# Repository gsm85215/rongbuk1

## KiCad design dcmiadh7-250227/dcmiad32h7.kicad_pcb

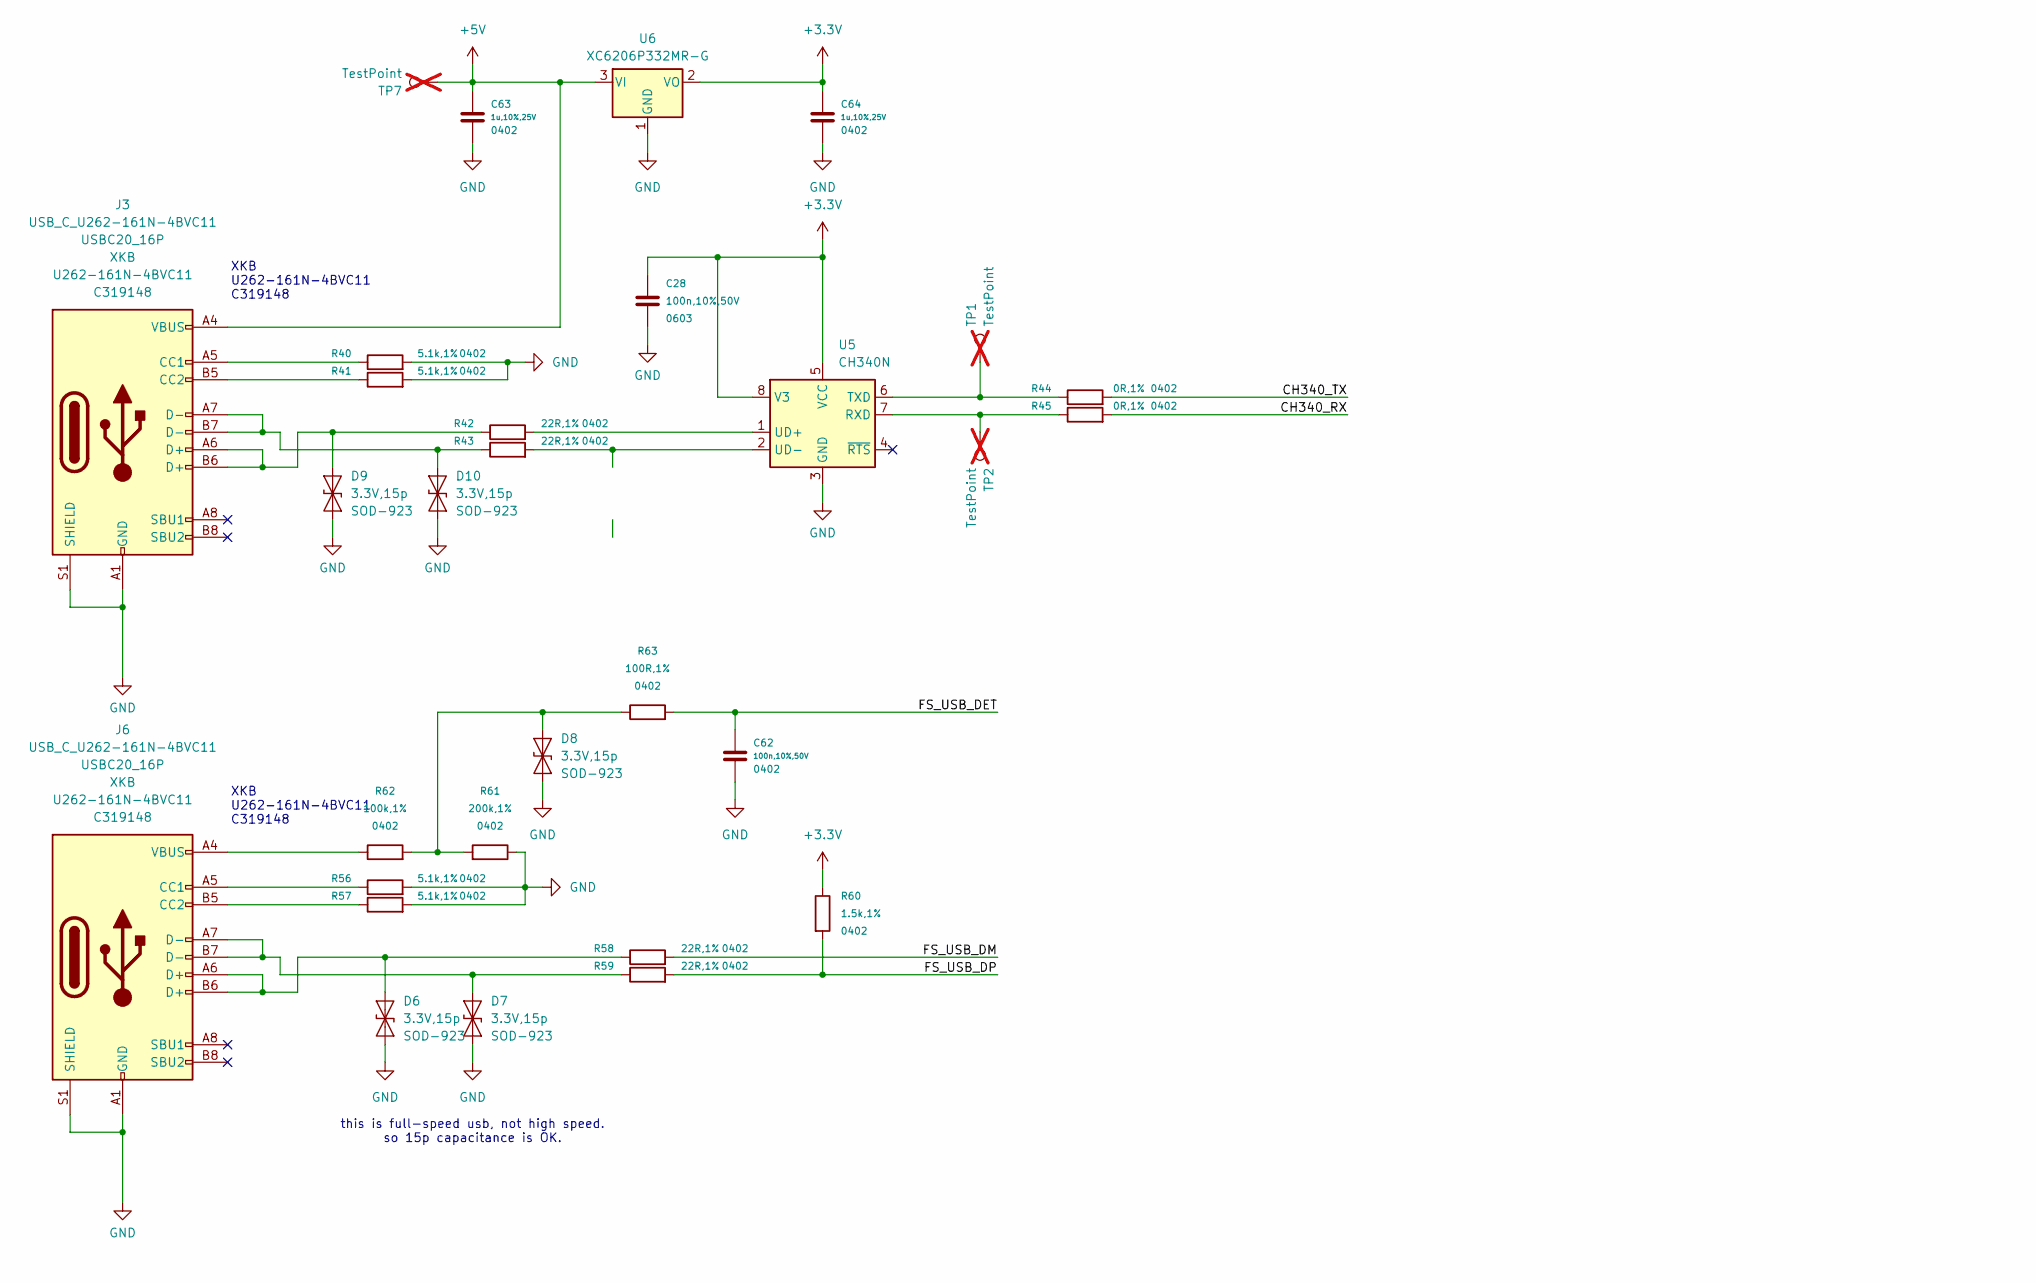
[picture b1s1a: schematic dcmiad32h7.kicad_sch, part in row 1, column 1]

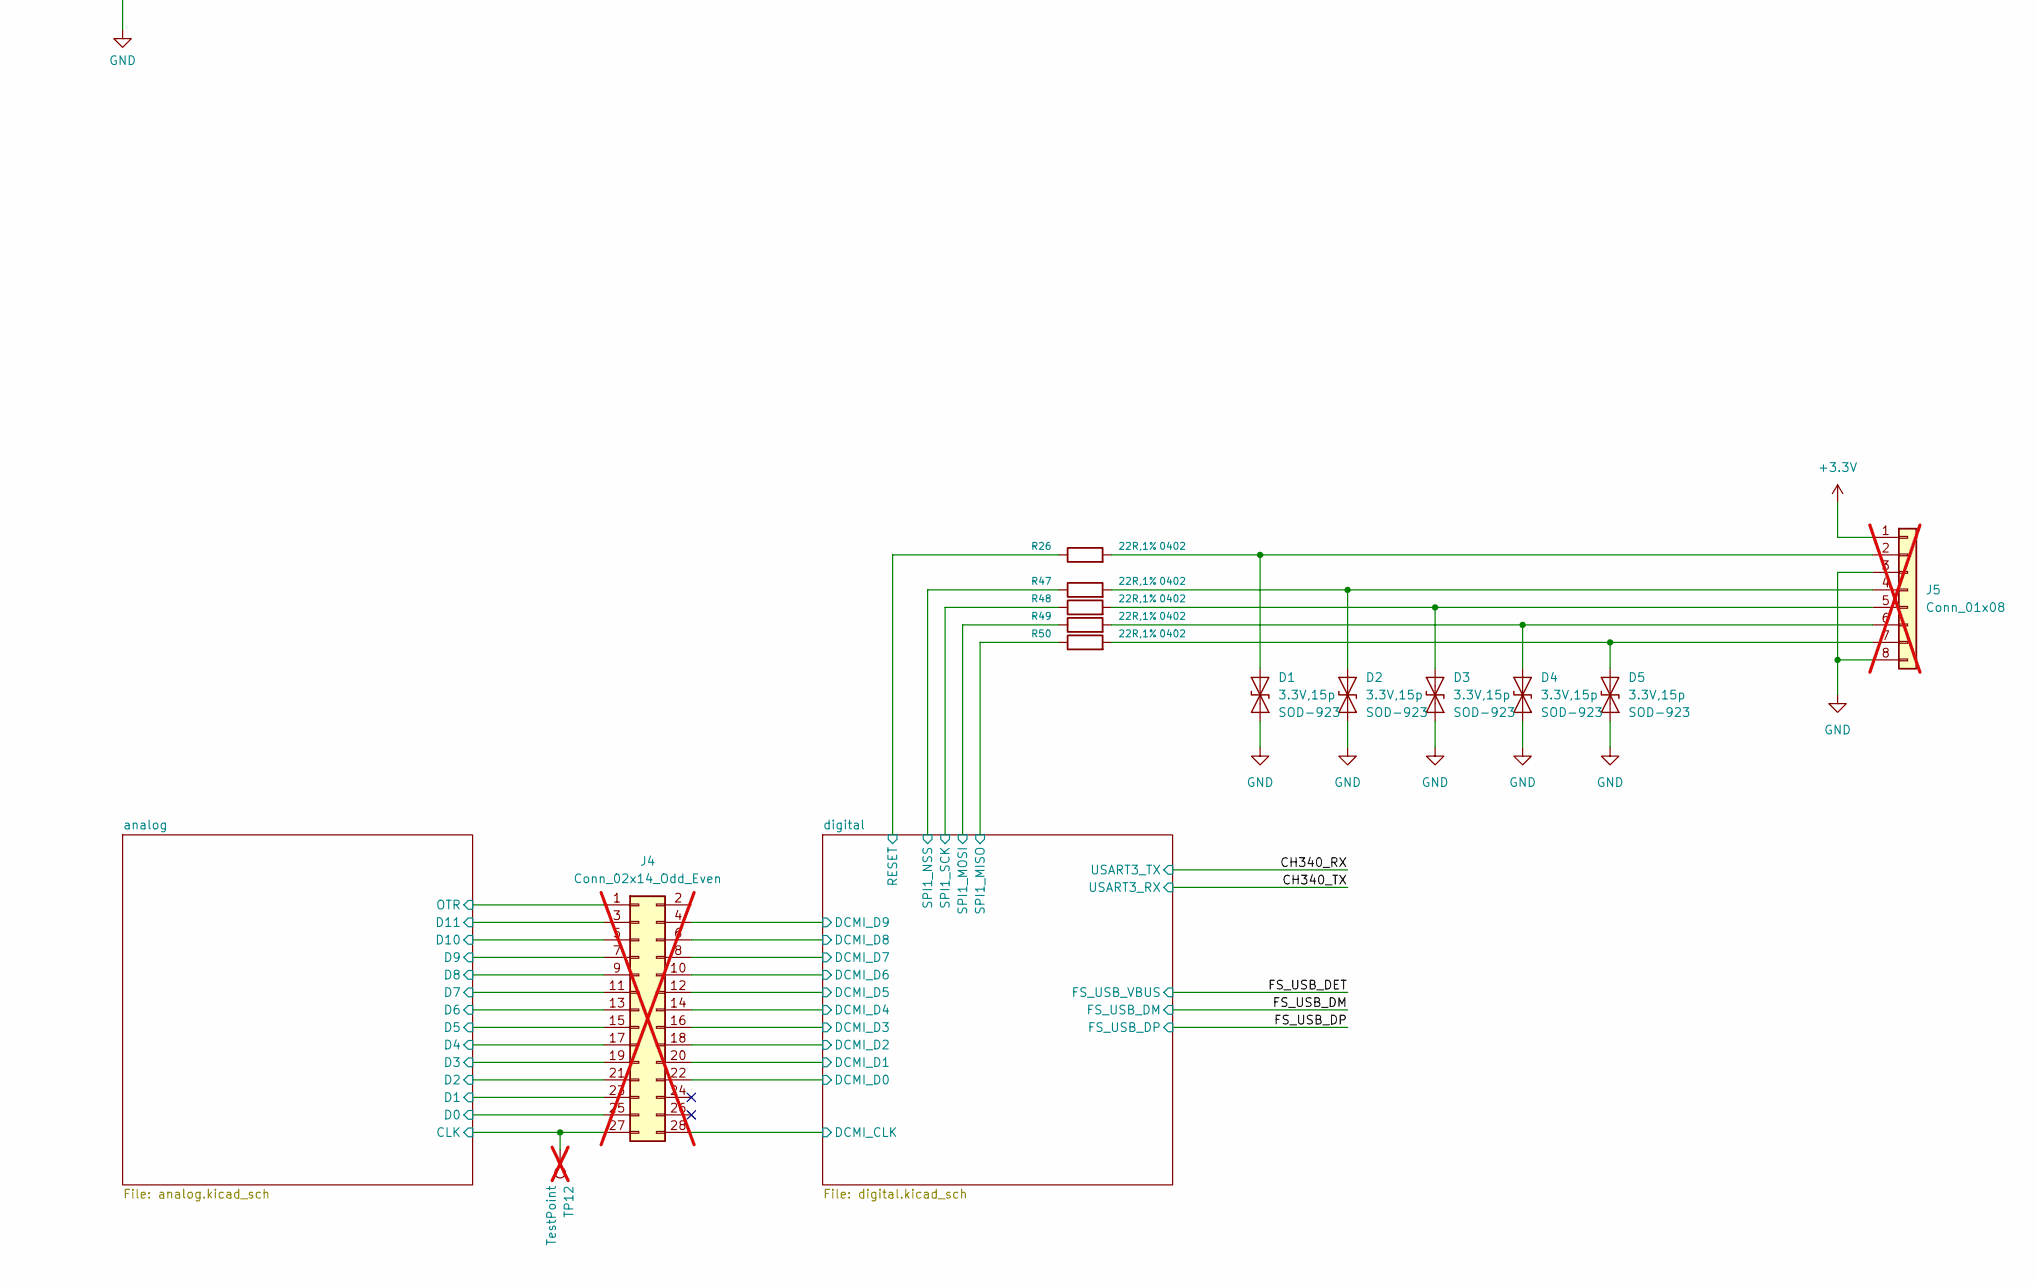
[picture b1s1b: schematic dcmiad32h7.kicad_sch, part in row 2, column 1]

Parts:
C28: 100n,10%,50V; C_0603_1608Metric_1.28x0.64mm_Courtyard; Manufacturer Part CC0603KRX7R9BB104
C62: 100n,10%,50V; C_0402_1005Metric_for_0.25mm_grid; Manufacturer Part CL05B104KB54PNC
C63, C64: 1u,10%,25V; C_0402_1005Metric_for_0.25mm_grid; Manufacturer Part CL05A105KA5NQNC
D1, D2, D3, D4, D5, D6, D7, D8, D9, D10: 3.3V,15p; D_SOD-923; Manufacturer Part ESD9B3.3ST5G
J3, J6: USB_C_U262-161N-4BVC11; USB_C_Receptacle_XKB_U262-16XN-4BVC11; Manufacturer Part U262-161N-4BVC11
J4: Conn_02x14_Odd_Even; PinHeader_2x14_P2.54mm_Vertical; not fitted
J5: Conn_01x08; PinHeader_1x08_P2.54mm_Vertical; not fitted
R26, R42, R43, R47, R48, R49, R50, R58, R59: 22R,1%; R_0402_1005Metric_for_0.25mm_grid; Manufacturer Part 0402WGF220JTCE
R40, R41, R56, R57: 5.1k,1%; R_0402_1005Metric_for_0.25mm_grid; Manufacturer Part 0402WGF5101TCE
R44, R45: 0R,1%; R_0402_1005Metric_for_0.25mm_grid; Manufacturer Part 0402WGF0000TCE
R60: 1.5k,1%; R_0402_1005Metric_for_0.25mm_grid; Manufacturer Part 0402WGF1501TCE
R61: 200k,1%; R_0402_1005Metric_for_0.25mm_grid; Manufacturer Part 0402WGF2003TCE
R62: 100k,1%; R_0402_1005Metric_for_0.25mm_grid; Manufacturer Part 0402WGF1003TCE
R63: 100R,1%; R_0402_1005Metric_for_0.25mm_grid; Manufacturer Part 0402WGF1000TCE
TP1, TP2, TP7, TP12: TestPoint; TestPoint_THTPad_D1.0mm_Drill0.5mm; not fitted
U5: CH340N; SOP-8_3.9x4.9mm_P1.27mm; Manufacturer Part CH340N
U6: XC6206P332MR-G; SOT-23; Manufacturer Part XC6206P332MR-G

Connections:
+3.3V: C28.1, C64.1, J5.1, R60.1, U5.5 (VCC), U5.8 (V3), U6.2 (VO); also elsewhere on the board
+5V: C63.1, J3.A4 (VBUS), J3.A9 (VBUS), J3.B4 (VBUS), J3.B9 (VBUS), TP7.1, U6.3 (VI)
/CH340_RX: R45.2; also elsewhere on the board
/CH340_TX: R44.2; also elsewhere on the board
/FS_USB_DET: C62.1, R63.2; also elsewhere on the board
/FS_USB_DM: R58.2; also elsewhere on the board
/FS_USB_DP: R59.2, R60.2; also elsewhere on the board
/analog/CLK: J4.27, TP12.1; also elsewhere on the board
/analog/D0: J4.25; also elsewhere on the board
/analog/D1: J4.23; also elsewhere on the board
/analog/D2: J4.21; also elsewhere on the board
/analog/D3: J4.19; also elsewhere on the board
/analog/D4: J4.17; also elsewhere on the board
/analog/D5: J4.15; also elsewhere on the board
/analog/D6: J4.13; also elsewhere on the board
/analog/D7: J4.11; also elsewhere on the board
/analog/D8: J4.9; also elsewhere on the board
/analog/D9: J4.7; also elsewhere on the board
/analog/D10: J4.5; also elsewhere on the board
/analog/D11: J4.3; also elsewhere on the board
/analog/OTR: J4.1; also elsewhere on the board
/digital/DCMI_D0: J4.22; also elsewhere on the board
/digital/DCMI_D1: J4.20; also elsewhere on the board
/digital/DCMI_D2: J4.18; also elsewhere on the board
/digital/DCMI_D3: J4.16; also elsewhere on the board
/digital/DCMI_D4: J4.14; also elsewhere on the board
/digital/DCMI_D5: J4.12; also elsewhere on the board
/digital/DCMI_D6: J4.10; also elsewhere on the board
/digital/DCMI_D7: J4.8; also elsewhere on the board
/digital/DCMI_D8: J4.6; also elsewhere on the board
/digital/DCMI_D9: J4.4; also elsewhere on the board
/digital/DCMI_PIXCLK: J4.28; also elsewhere on the board
/digital/SPI1_MISO: R50.1; also elsewhere on the board
/digital/SPI1_MOSI: R49.1; also elsewhere on the board
/digital/SPI1_NSS: R47.1; also elsewhere on the board
/digital/SPI1_SCK: R48.1; also elsewhere on the board
/digital/STM32_NRST: R26.1; also elsewhere on the board
GND: C28.2, C62.2, C63.2, C64.2, D1.1 (A1), D2.1 (A1), D3.1 (A1), D4.1 (A1), D5.1 (A1), D6.1 (A1), D7.1 (A1), D8.1 (A1), D9.1 (A1), D10.1 (A1), J3.A1 (GND), J3.A12 (GND), J3.B1 (GND), J3.B12 (GND), J3.S1 (SHIELD), J5.3, J5.8, J6.A1 (GND), J6.A12 (GND), J6.B1 (GND), J6.B12 (GND), J6.S1 (SHIELD), R40.2, R41.2, R56.2, R57.2, R61.1, U5.3 (GND), U6.1 (GND); also elsewhere on the board
unnamed: D1.2 (A2), J5.2, R26.2
unnamed: D2.2 (A2), J5.4, R47.2
unnamed: D3.2 (A2), J5.5, R48.2
unnamed: D4.2 (A2), J5.6, R49.2
unnamed: D5.2 (A2), J5.7, R50.2
unnamed: D6.2 (A2), J6.A6 (D+), J6.B6 (D+), R58.1
unnamed: D7.2 (A2), J6.A7 (D-), J6.B7 (D-), R59.1
unnamed: D8.2 (A2), R61.2, R62.2, R63.1
unnamed: D9.2 (A2), J3.A6 (D+), J3.B6 (D+), R42.1
unnamed: D10.2 (A2), J3.A7 (D-), J3.B7 (D-), R43.1
unnamed: J3.A5 (CC1), R40.1
unnamed: J3.B5 (CC2), R41.1
unnamed: J6.A5 (CC1), R56.1
unnamed: J6.B5 (CC2), R57.1
unnamed: J6.A4 (VBUS), J6.A9 (VBUS), J6.B4 (VBUS), J6.B9 (VBUS), R62.1
unnamed: R45.1, TP2.1, U5.7 (RXD)
unnamed: R44.1, TP1.1, U5.6 (TXD)
unnamed: R42.2, U5.1 (UD+)
unnamed: R43.2, U5.2 (UD-)

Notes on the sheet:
XKB U262-161N-4BVC11 C319148
this is full-speed usb, not high speed. so 15p capacitance is OK.

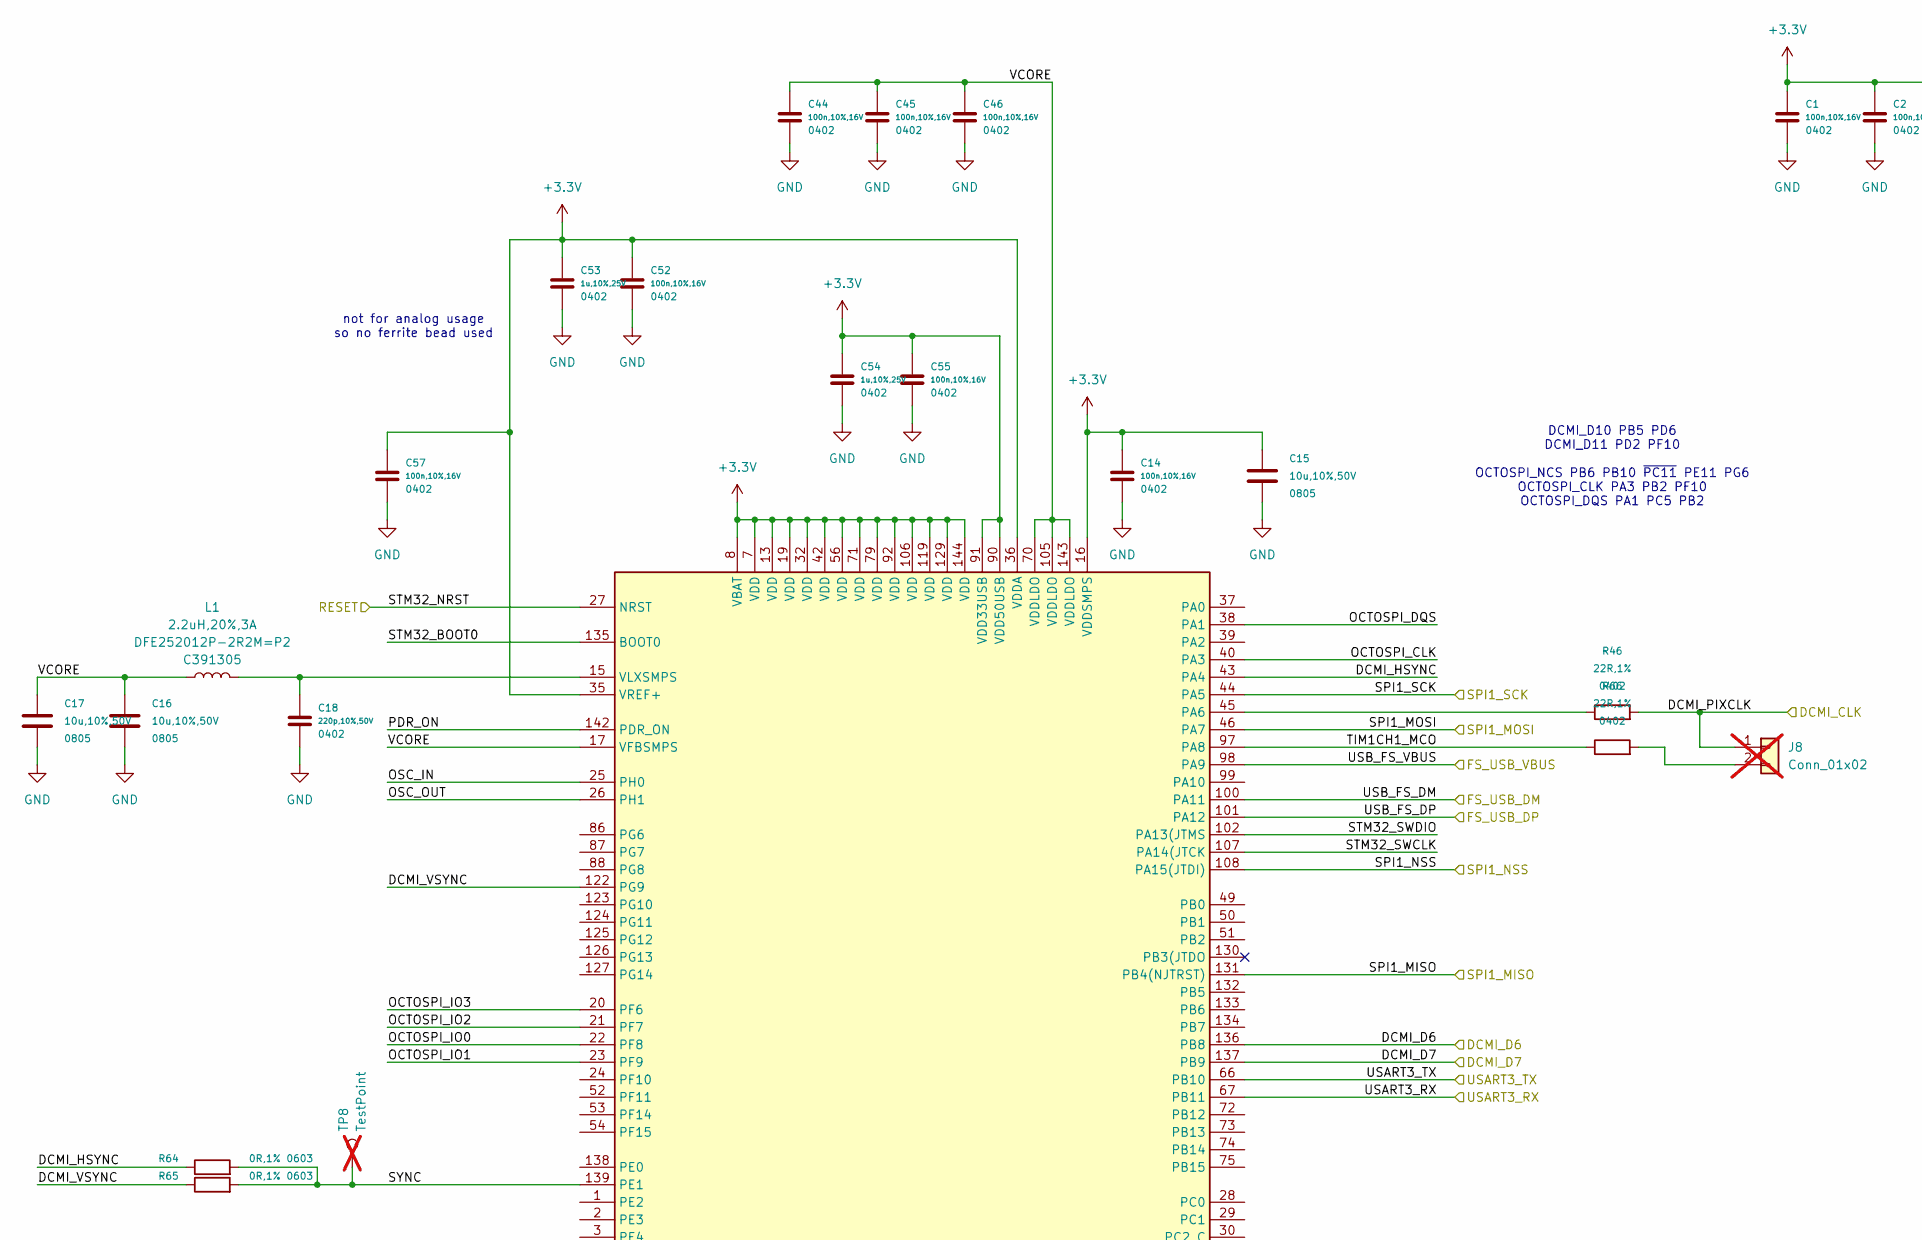
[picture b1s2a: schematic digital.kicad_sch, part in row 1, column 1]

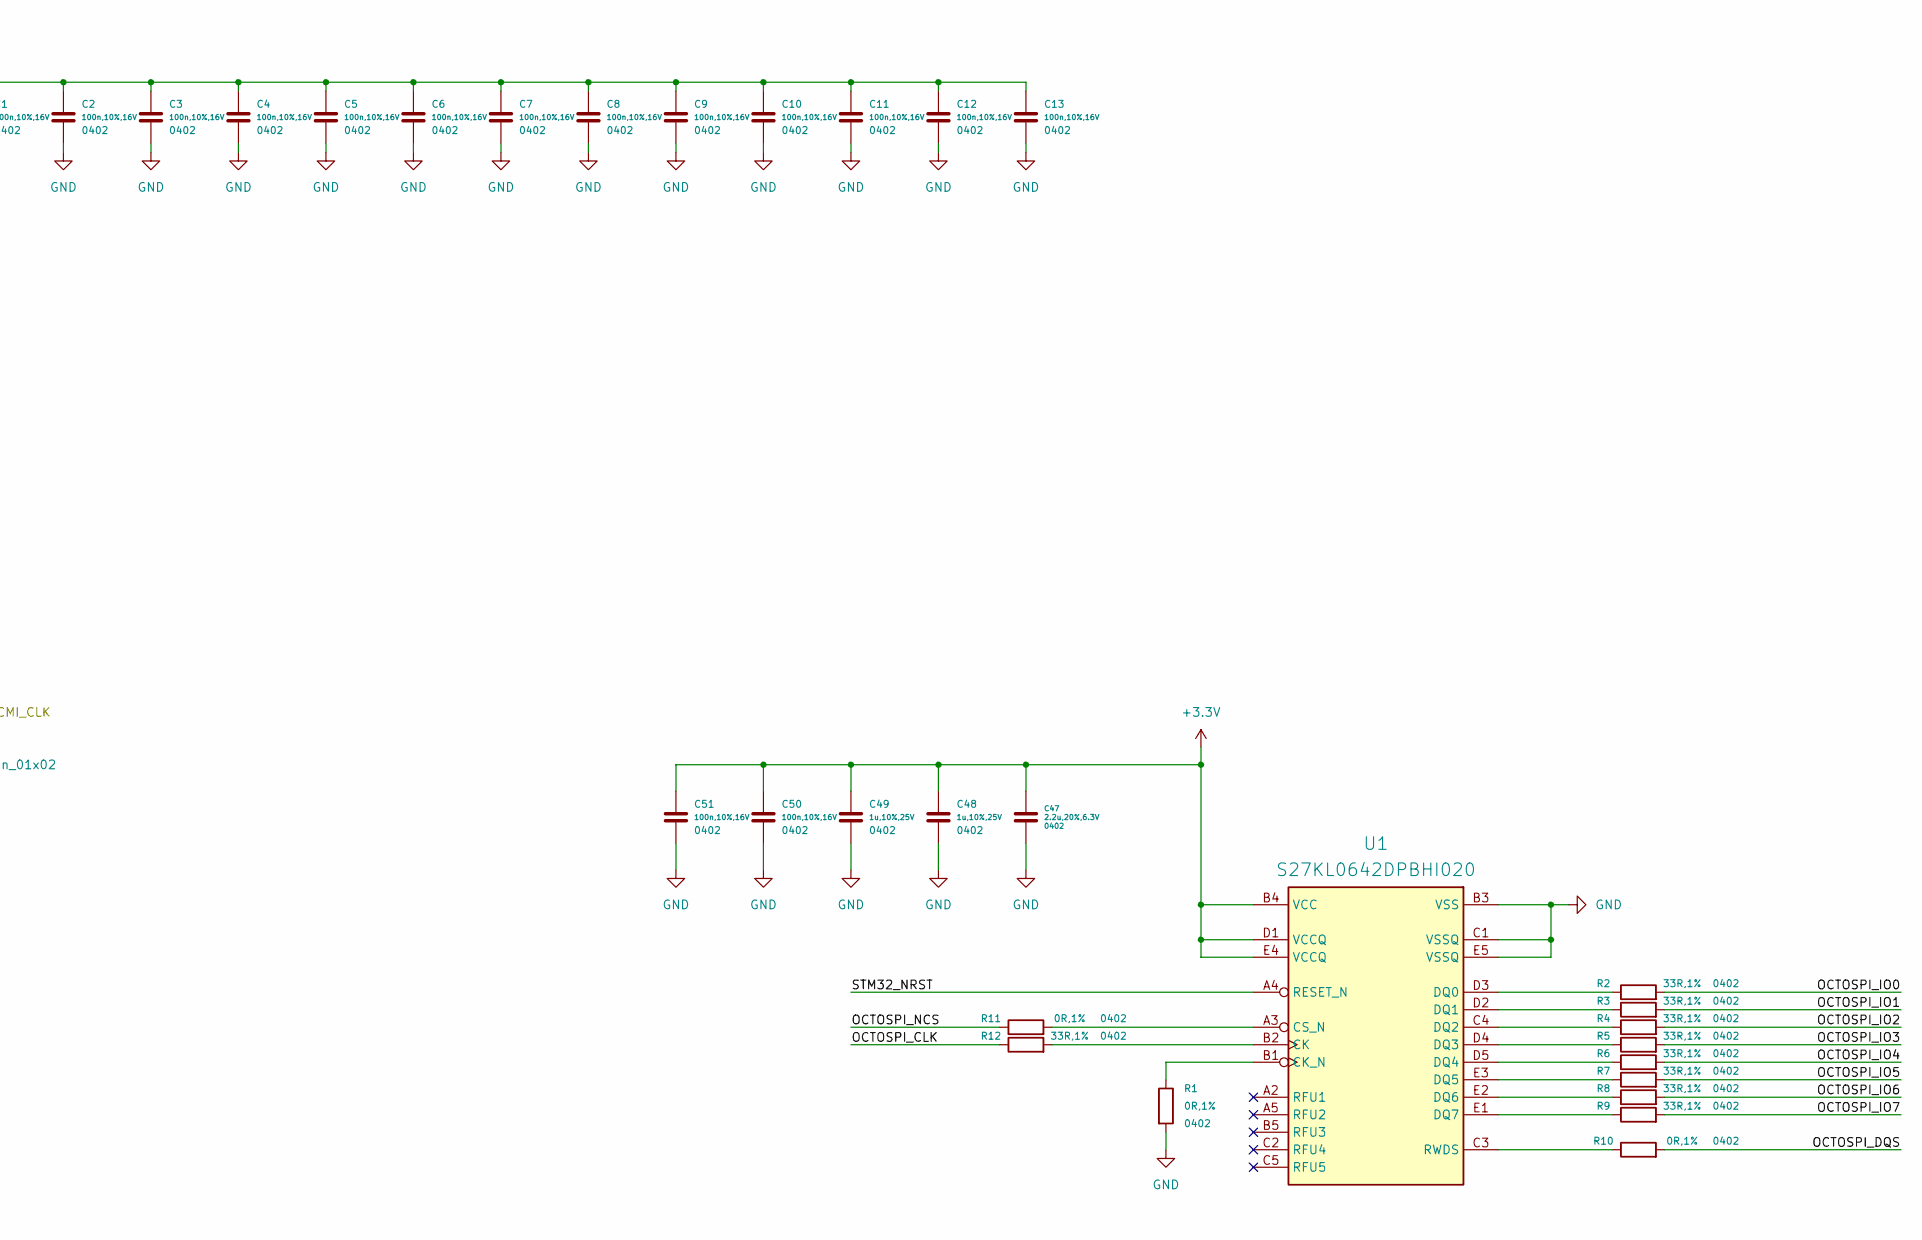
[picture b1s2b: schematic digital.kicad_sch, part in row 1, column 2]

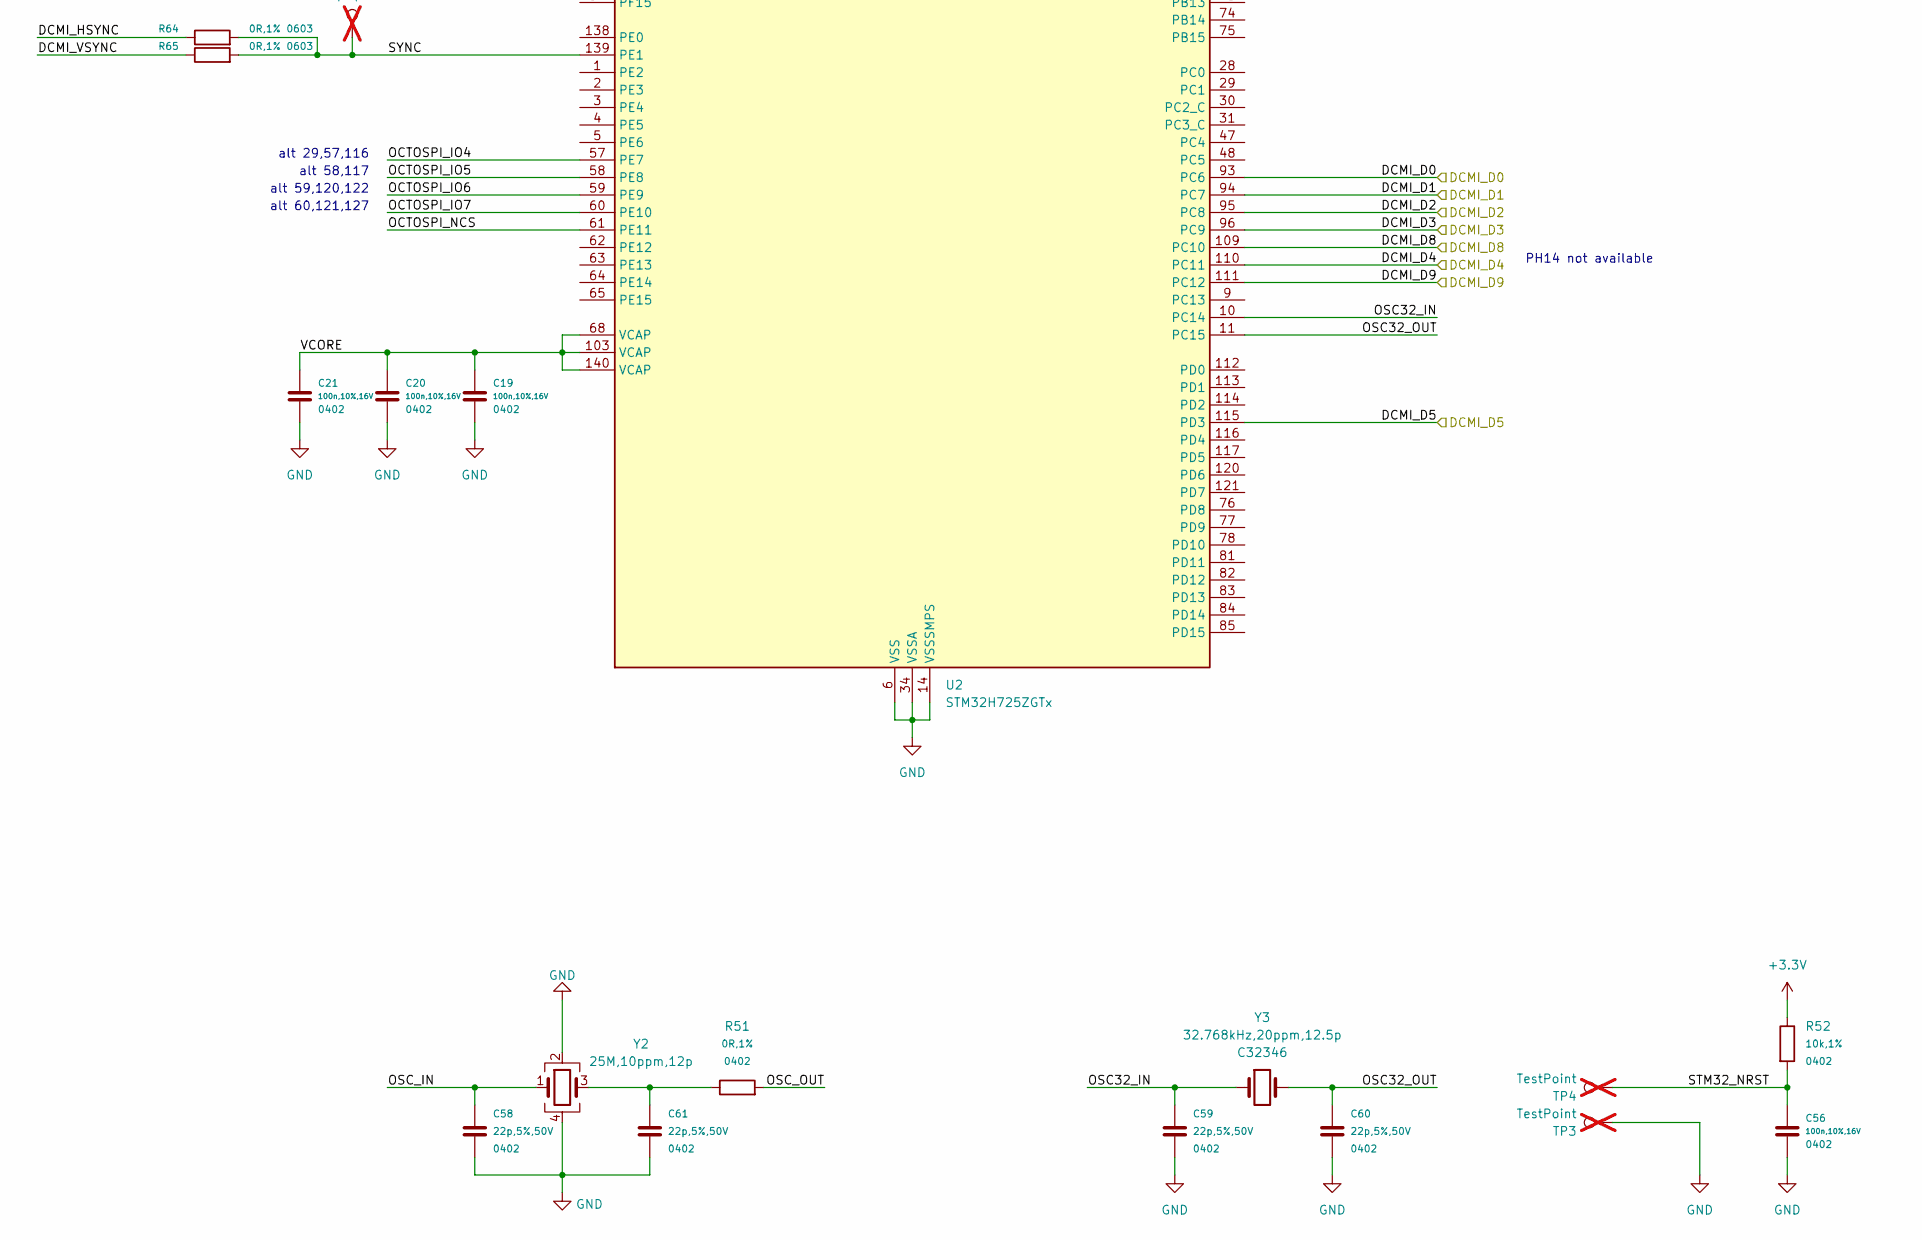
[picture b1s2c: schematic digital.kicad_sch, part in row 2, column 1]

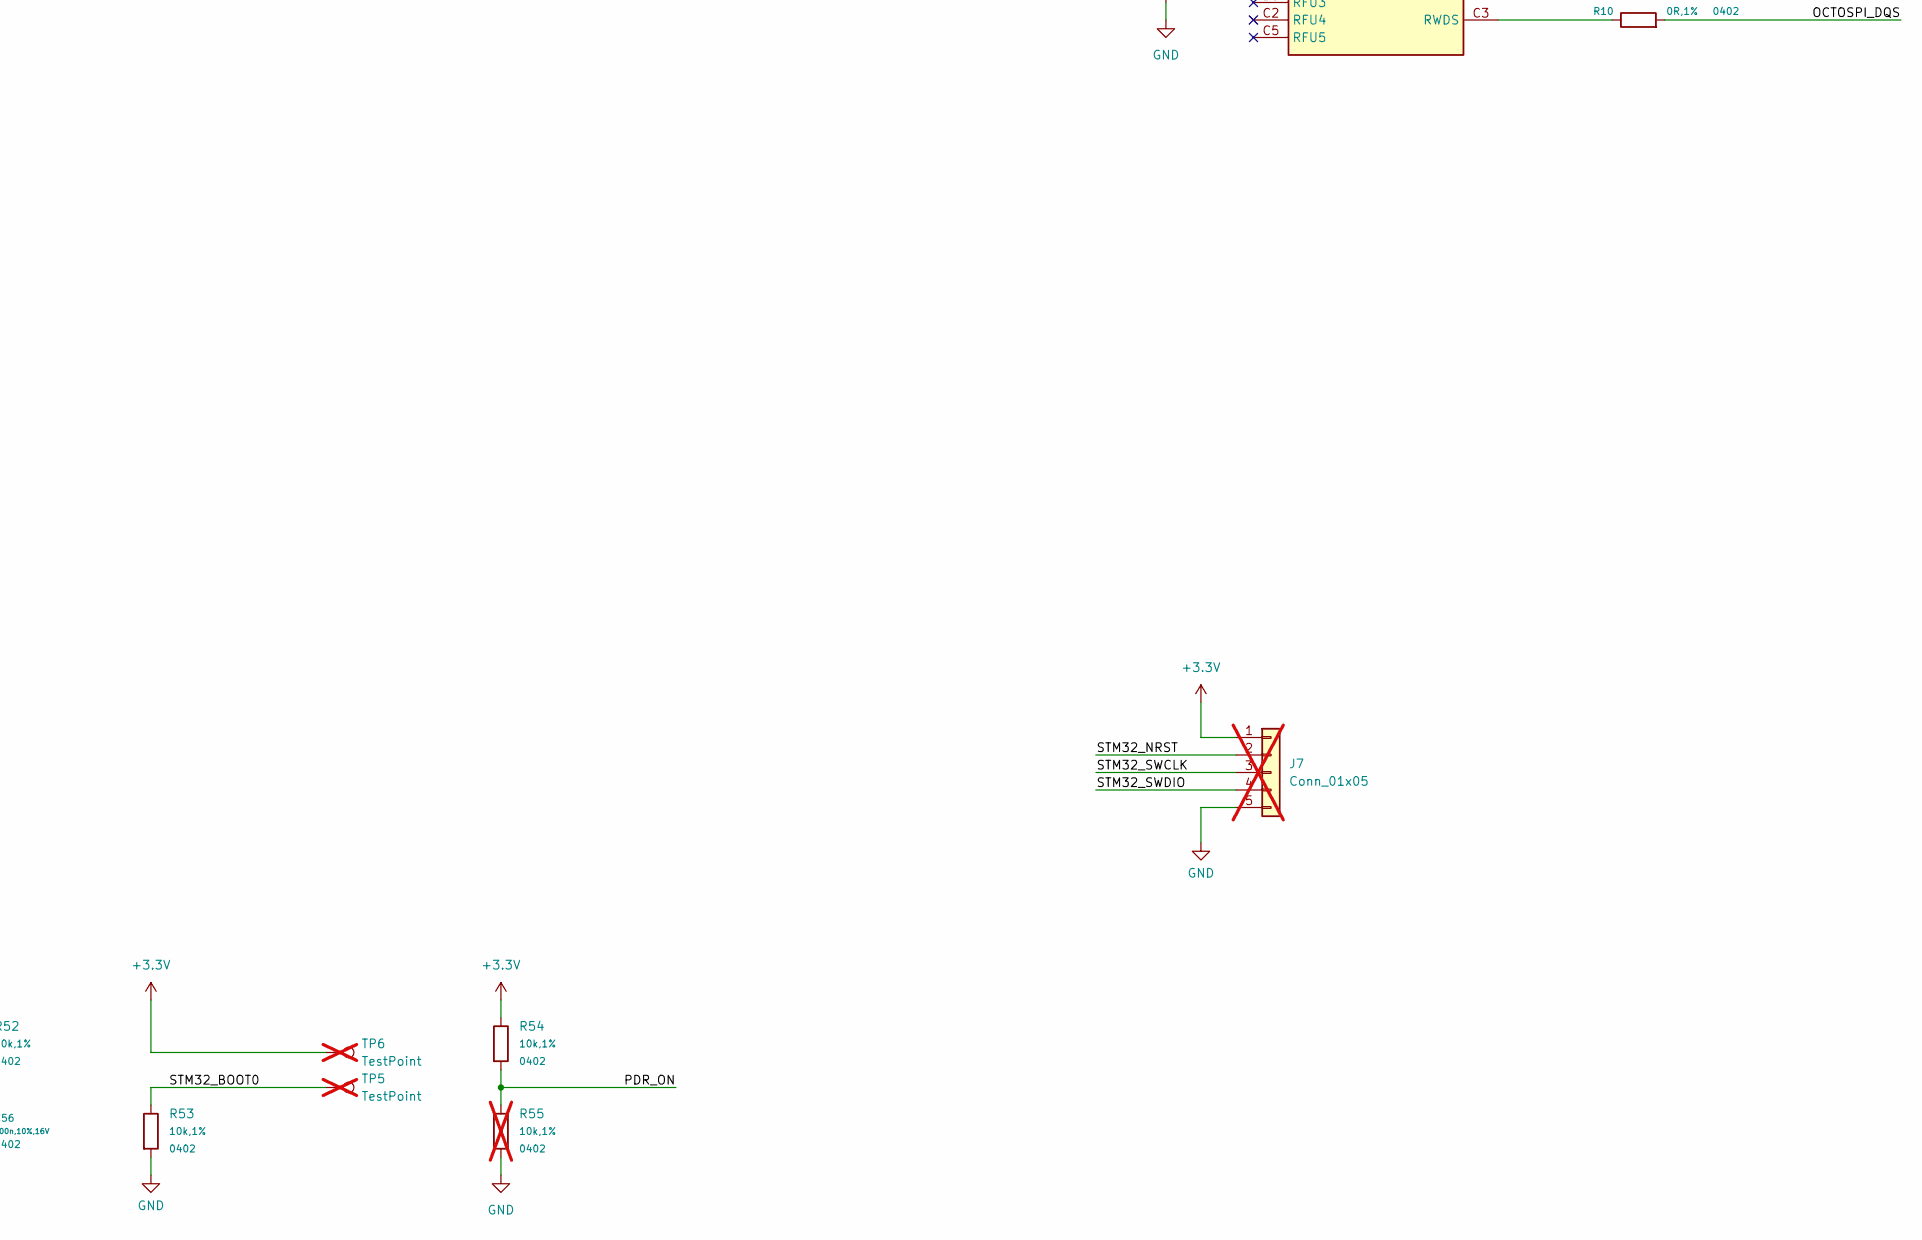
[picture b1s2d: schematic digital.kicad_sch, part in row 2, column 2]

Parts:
C1, C2, C3, C4, C5, C6, C7, C8, C9, C10, C11, C12, C13, C14, C19, C20, C21, C44, C45, C46, C50, C51, C52, C55, C56, C57: 100n,10%,16V; C_0402_1005Metric_for_0.25mm_grid; Manufacturer Part CL05B104KO5NNNC
C15, C16, C17: 10u,10%,50V; C_0805_2012Metric; Manufacturer Part GRM21BR61H106KE43L
C18: 220p,10%,50V; C_0402_1005Metric_for_0.25mm_grid; Manufacturer Part 0402B221K500NT
C47: 2.2u,20%,6.3V; C_0402_1005Metric_for_0.25mm_grid; Manufacturer Part CL05A225MQ5NSNC
C48, C49, C53, C54: 1u,10%,25V; C_0402_1005Metric_for_0.25mm_grid; Manufacturer Part CL05A105KA5NQNC
C58, C59, C60, C61: 22p,5%,50V; C_0402_1005Metric_for_0.25mm_grid; Manufacturer Part 0402CG220J500NT
J7: Conn_01x05; PinHeader_1x05_P2.54mm_Vertical; Manufacturer Part PZ254R-11-05P; not fitted
J8: Conn_01x02; PinHeader_1x02_P2.54mm_Vertical; not fitted
L1: 2.2uH,20%,3A; L_1008_2520Metric; Manufacturer Part DFE252012P-2R2M=P2
R1, R10, R11, R51: 0R,1%; R_0402_1005Metric_for_0.25mm_grid; Manufacturer Part 0402WGF0000TCE
R2, R3, R4, R5, R6, R7, R8, R9, R12: 33R,1%; R_0402_1005Metric_for_0.25mm_grid; Manufacturer Part 0402WGF330JTCE
R46, R66: 22R,1%; R_0402_1005Metric_for_0.25mm_grid; Manufacturer Part 0402WGF220JTCE
R52, R53, R54: 10k,1%; R_0402_1005Metric_for_0.25mm_grid; Manufacturer Part 0402WGF1002TCE
R55: 10k,1%; R_0402_1005Metric_for_0.25mm_grid; Manufacturer Part 0402WGF1002TCE; not fitted
R64, R65: 0R,1%; R_0603_1608Metric_1.28x0.64mm_Courtyard; Manufacturer Part 0603WAF0000T5E
TP3, TP4, TP5, TP6, TP8: TestPoint; TestPoint_THTPad_D1.0mm_Drill0.5mm; not fitted
U1: S27KL0642DPBHI020; BGA-24_6x8mm_Layout5x5_P1.0mm; Manufacturer Part S27KL0642DPBHI020
U2: STM32H725ZGTx; LQFP-144_20x20mm_P0.5mm
Y2: 25M,10ppm,12p; Crystal_SMD_3225-4Pin_3.2x2.5mm; Manufacturer Part X322525MOB4SI
Y3: 32.768kHz,20ppm,12.5p; Crystal_SMD_3215-2Pin_3.2x1.5mm; Manufacturer Part Q13FC13500004

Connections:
+3.3V: C1.1, C2.1, C3.1, C4.1, C5.1, C6.1, C7.1, C8.1, C9.1, C10.1, C11.1, C12.1, C13.1, C14.1, C15.1, C47.1, C48.1, C49.1, C50.1, C51.1, C52.1, C53.1, C54.1, C55.1, C57.1, J7.1, R52.1, R54.1, TP6.1, U1.B4 (VCC), U1.D1 (VCCQ), U1.E4 (VCCQ), U2.7 (VDD), U2.8 (VBAT), U2.13 (VDD), U2.16 (VDDSMPS), U2.19 (VDD), U2.32 (VDD), U2.35 (VREF+), U2.36 (VDDA), U2.42 (VDD), U2.56 (VDD), U2.71 (VDD), U2.79 (VDD), U2.90 (VDD50USB), U2.91 (VDD33USB), U2.92 (VDD), U2.106 (VDD), U2.119 (VDD), U2.129 (VDD), U2.144 (VDD); also elsewhere on the board
/CH340_RX: U2.66 (PB10); also elsewhere on the board
/CH340_TX: U2.67 (PB11); also elsewhere on the board
/FS_USB_DET: U2.98 (PA9); also elsewhere on the board
/FS_USB_DM: U2.100 (PA11); also elsewhere on the board
/FS_USB_DP: U2.101 (PA12); also elsewhere on the board
/digital/DCMI_D0: U2.93 (PC6); also elsewhere on the board
/digital/DCMI_D1: U2.94 (PC7); also elsewhere on the board
/digital/DCMI_D2: U2.95 (PC8); also elsewhere on the board
/digital/DCMI_D3: U2.96 (PC9); also elsewhere on the board
/digital/DCMI_D4: U2.110 (PC11); also elsewhere on the board
/digital/DCMI_D5: U2.115 (PD3); also elsewhere on the board
/digital/DCMI_D6: U2.136 (PB8); also elsewhere on the board
/digital/DCMI_D7: U2.137 (PB9); also elsewhere on the board
/digital/DCMI_D8: U2.109 (PC10); also elsewhere on the board
/digital/DCMI_D9: U2.111 (PC12); also elsewhere on the board
/digital/DCMI_HSYNC: R64.1, U2.43 (PA4)
/digital/DCMI_PIXCLK: J8.1, R46.2; also elsewhere on the board
/digital/DCMI_VSYNC: R65.1, U2.122 (PG9)
/digital/OCTOSPI_CLK: R12.1, U2.40 (PA3)
/digital/OCTOSPI_DQS: R10.2, U2.38 (PA1)
/digital/OCTOSPI_IO0: R2.2, U2.22 (PF8)
/digital/OCTOSPI_IO1: R3.2, U2.23 (PF9)
/digital/OCTOSPI_IO2: R4.2, U2.21 (PF7)
/digital/OCTOSPI_IO3: R5.2, U2.20 (PF6)
/digital/OCTOSPI_IO4: R6.2, U2.57 (PE7)
/digital/OCTOSPI_IO5: R7.2, U2.58 (PE8)
/digital/OCTOSPI_IO6: R8.2, U2.59 (PE9)
/digital/OCTOSPI_IO7: R9.2, U2.60 (PE10)
/digital/OCTOSPI_NCS: R11.1, U2.61 (PE11)
/digital/OSC32_IN: C59.1, U2.10 (PC14), Y3.1
/digital/OSC32_OUT: C60.1, U2.11 (PC15), Y3.2
/digital/OSC_IN: C58.1, U2.25 (PH0), Y2.1
/digital/OSC_OUT: R51.2, U2.26 (PH1)
/digital/PDR_ON: R54.2, R55.1, U2.142 (PDR_ON)
/digital/SPI1_MISO: U2.131 (PB4(NJTRST)); also elsewhere on the board
/digital/SPI1_MOSI: U2.46 (PA7); also elsewhere on the board
/digital/SPI1_NSS: U2.108 (PA15(JTDI)); also elsewhere on the board
/digital/SPI1_SCK: U2.44 (PA5); also elsewhere on the board
/digital/STM32_BOOT0: R53.1, TP5.1, U2.135 (BOOT0)
/digital/STM32_NRST: C56.1, J7.2, R52.2, TP4.1, U1.A4 (RESET_N), U2.27 (NRST); also elsewhere on the board
/digital/STM32_SWCLK: J7.3, U2.107 (PA14(JTCK)
/digital/STM32_SWDIO: J7.4, U2.102 (PA13(JTMS)
/digital/SYNC: R64.2, R65.2, TP8.1, U2.139 (PE1)
/digital/TIM1CH1_MCO: R66.1, U2.97 (PA8)
/digital/VCORE: C16.1, C17.1, C19.1, C20.1, C21.1, C44.1, C45.1, C46.1, L1.1, U2.17 (VFBSMPS), U2.68 (VCAP), U2.70 (VDDLDO), U2.103 (VCAP), U2.105 (VDDLDO), U2.140 (VCAP), U2.143 (VDDLDO)
GND: C1.2, C2.2, C3.2, C4.2, C5.2, C6.2, C7.2, C8.2, C9.2, C10.2, C11.2, C12.2, C13.2, C14.2, C15.2, C16.2, C17.2, C18.2, C19.2, C20.2, C21.2, C44.2, C45.2, C46.2, C47.2, C48.2, C49.2, C50.2, C51.2, C52.2, C53.2, C54.2, C55.2, C56.2, C57.2, C58.2, C59.2, C60.2, C61.2, J7.5, R1.2, R53.2, R55.2, TP3.1, U1.B3 (VSS), U1.C1 (VSSQ), U1.E5 (VSSQ), U2.6 (VSS), U2.12 (VSS), U2.14 (VSSSMPS), U2.18 (VSS), U2.33 (VSS), U2.34 (VSSA), U2.41 (VSS), U2.55 (VSS), U2.69 (VSS), U2.80 (VSS), U2.89 (VSS), U2.104 (VSS), U2.118 (VSS), U2.128 (VSS), U2.141 (VSS), Y2.2, Y2.4; also elsewhere on the board
unnamed: C61.1, R51.1, Y2.3
unnamed: J8.2, R66.2
unnamed: R12.2, U1.B2 (CK)
unnamed: R1.1, U1.B1 (CK_N)
unnamed: R11.2, U1.A3 (CS_N)
unnamed: R2.1, U1.D3 (DQ0)
unnamed: R3.1, U1.D2 (DQ1)
unnamed: R4.1, U1.C4 (DQ2)
unnamed: R5.1, U1.D4 (DQ3)
unnamed: R6.1, U1.D5 (DQ4)
unnamed: R7.1, U1.E3 (DQ5)
unnamed: R8.1, U1.E2 (DQ6)
unnamed: R9.1, U1.E1 (DQ7)
unnamed: R10.1, U1.C3 (RWDS)
unnamed: R46.1, U2.45 (PA6)
unnamed: C18.1, L1.2, U2.15 (VLXSMPS)

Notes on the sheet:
DCMI_D10 PB5 PD6 DCMI_D11 PD2 PF10 OCTOSPI_NCS PB6 PB10 ~{PC11} PE11 PG6 OCTOSPI_CLK PA3 PB2 PF10 OCTOSPI_DQS PA1 PC5 PB2
alt 29,57,116
alt 60,121,127
alt 59,120,122
not for analog usage so no ferrite bead used
PH14 not available
alt 58,117
